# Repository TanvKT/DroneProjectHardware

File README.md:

# DroneProjectHardware
PCB schematic and design for Drone Project

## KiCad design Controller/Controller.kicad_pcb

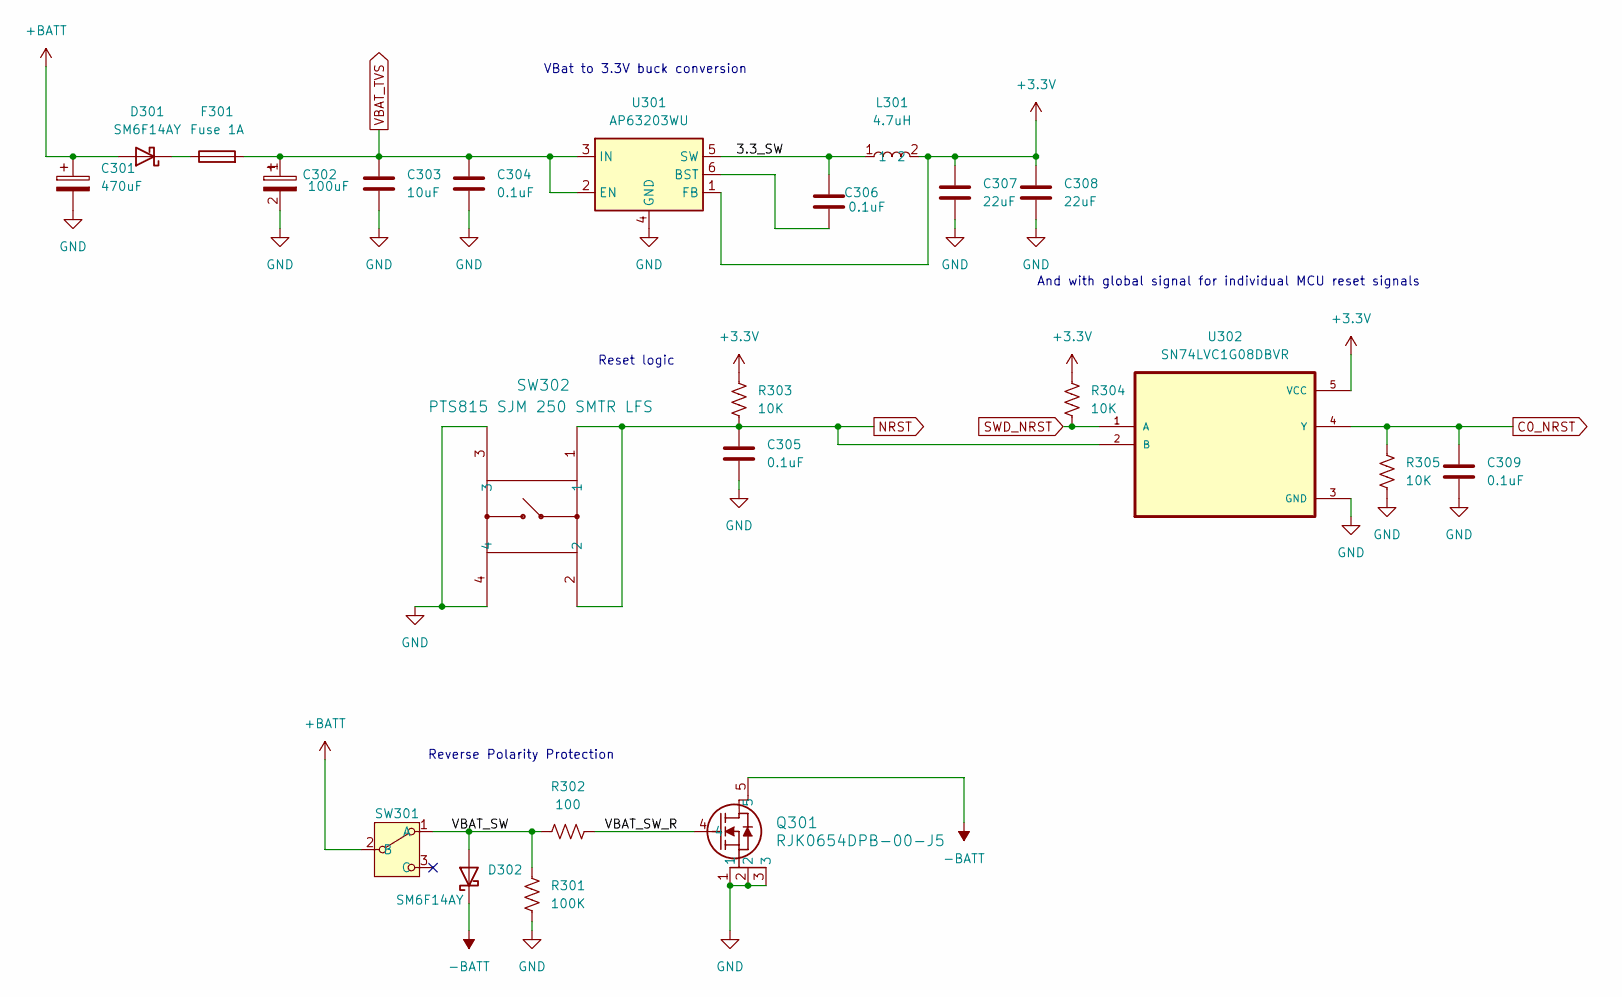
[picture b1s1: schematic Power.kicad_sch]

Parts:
C301: 470uF; CP_Elec_10x10.5
C302: 100uF; CAP_A768EB_6.8x6.8_KEM
C303: 10uF; C_1206_3216Metric
C304, C305, C306, C309: 0.1uF; C_0402_1005Metric
C307, C308: 22uF; C_0603_1608Metric
D301, D302: SM6F14AY; D_SOD-128
F301: Fuse 1A; Fuse_1812_4532Metric
L301: 4.7uH; IND_VLS6045EX-4R7M_TDK
Q301: RJK0654DPB-00-J5; LFPAK_REN
R301: 100K; R_0402_1005Metric
R302: 100; R_0201_0603Metric
R303, R304, R305: 10K; R_0402_1005Metric
SW301: SW_EG1218
SW302: PTS815 SJM 250 SMTR LFS; SW4_PTS815 SJM 250 SMTR LFS_CNK
U301: AP63203WU; TSOT-23-6
U302: SN74LVC1G08DBVR; SOT95P280X145-5N

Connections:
+3.3V: C307.1, C308.1, L301.2, R303.2, R304.2, U301.1 (FB), U302.5 (VCC); also elsewhere on the board
+BATT: C301.1, D301.2 (A), SW301.2 (B); also elsewhere on the board
-BATT: D302.1 (K), Q301.5; also elsewhere on the board
/Power/3.3_SW: C306.2, L301.1, U301.5 (SW)
/Power/VBAT_SW: D302.2 (A), R301.1, R302.1, SW301.1 (A)
/Power/VBAT_SW_R: Q301.4, R302.2
C0_NRST: C309.1, R305.2, U302.4 (Y); also elsewhere on the board
GND: C301.2, C302.2, C303.2, C304.2, C305.2, C307.2, C308.2, C309.2, Q301.1, Q301.2, Q301.3, R301.2, R305.1, SW302.3, SW302.4, U301.4 (GND), U302.3 (GND); also elsewhere on the board
NRST: C305.1, R303.1, SW302.1, SW302.2, U302.2 (B)
unnamed: D301.1 (K), F301.1
unnamed: C306.1, U301.6 (BST)
SWD_NRST: R304.1, U302.1 (A); also elsewhere on the board
VBAT_TVS: C302.1, C303.1, C304.1, F301.2, U301.2 (EN), U301.3 (IN); also elsewhere on the board

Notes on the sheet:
Reverse Polarity Protection
VBat to 3.3V buck conversion
And with global signal for individual MCU reset signals
Reset logic

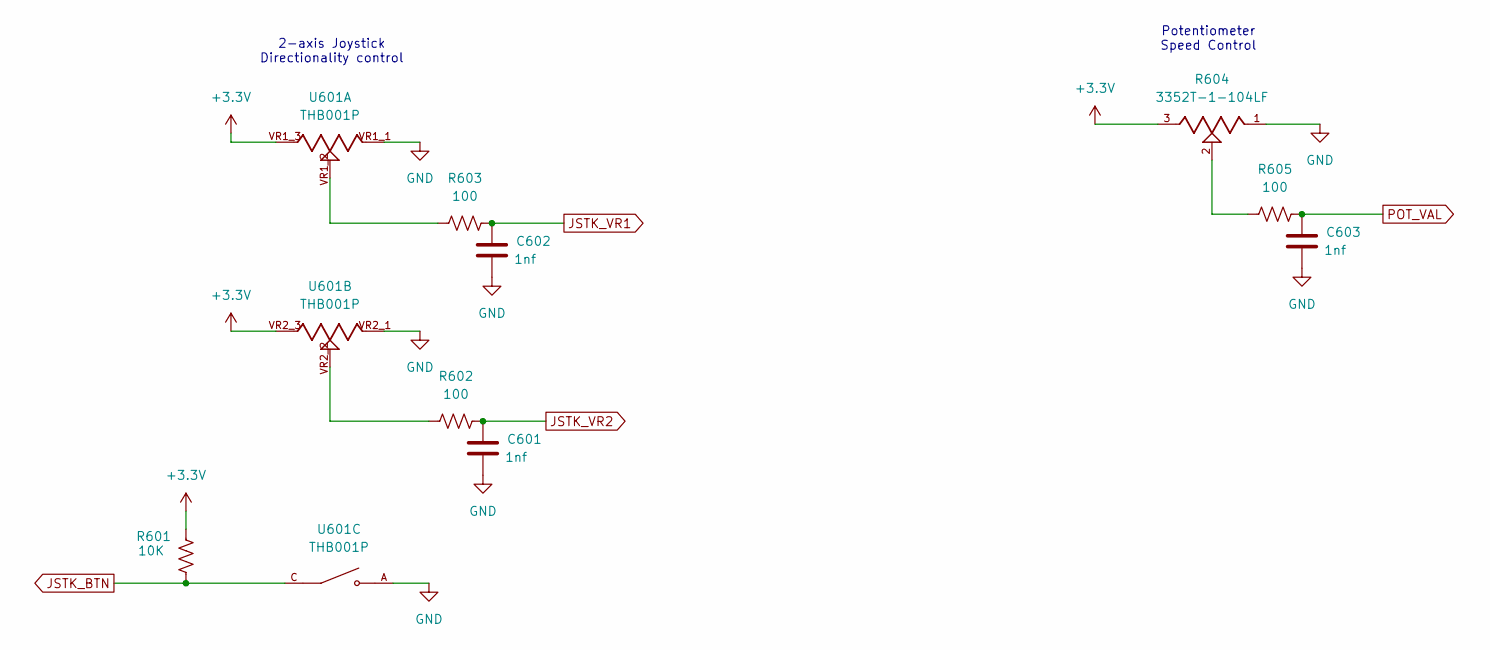
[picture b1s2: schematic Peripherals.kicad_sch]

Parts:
C601, C602, C603: 1nf; C_0402_1005Metric
R601: 10K; R_0402_1005Metric
R602, R603, R605: 100; R_0402_1005Metric
R604: 3352T-1-104LF; TRIM_3352T-1-104LF; PARTREV 08/19
U601: THB001P; CNK_THB001P; PARTREV 27 Jan 22

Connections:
+3.3V: R601.2, R604.3, U601.VR1_3, U601.VR2_3; also elsewhere on the board
GND: C601.2, C602.2, C603.2, R604.1, U601.A, U601.VR1_1, U601.VR2_1; also elsewhere on the board
JSTK_BTN: R601.1, U601.C; also elsewhere on the board
JSTK_VR1: C602.1, R603.2; also elsewhere on the board
JSTK_VR2: C601.1, R602.2; also elsewhere on the board
unnamed: R602.1, U601.VR2_2
unnamed: R603.1, U601.VR1_2
unnamed: R604.2, R605.1
POT_VAL: C603.1, R605.2; also elsewhere on the board

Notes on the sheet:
2-axis Joystick Directionality control
Potentiometer Speed Control

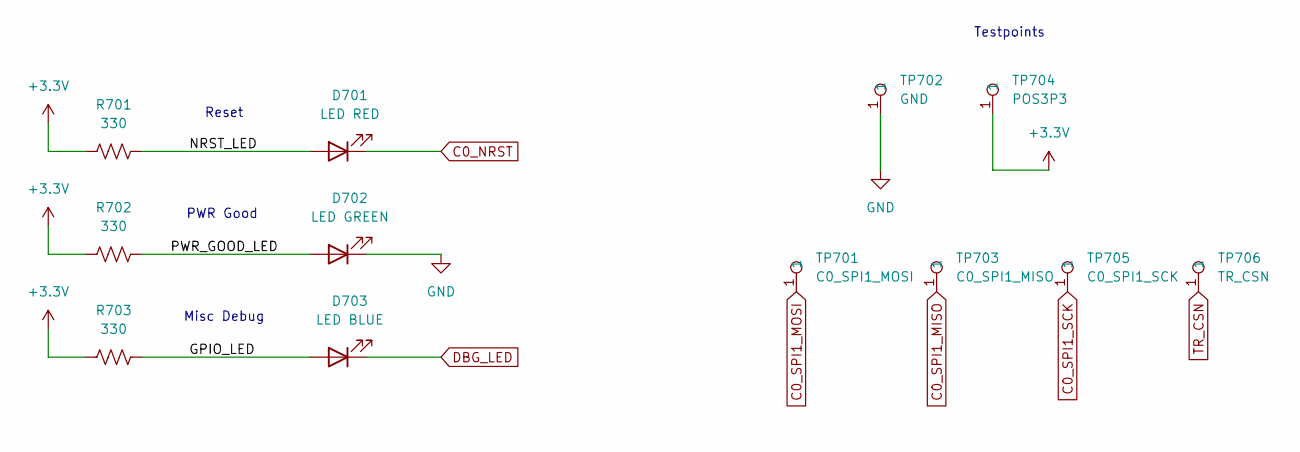
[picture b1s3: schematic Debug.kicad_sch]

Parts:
D701: LED RED; LED_0603_1608Metric
D702: LED GREEN; LED_0603_1608Metric
D703: LED BLUE; LED_0603_1608Metric
R701, R702, R703: 330; R_0402_1005Metric
TP701: C0_SPI1_MOSI; Testpoint 1.6mm x 0.8mm
TP702: GND; Testpoint 1.6mm x 0.8mm
TP703: C0_SPI1_MISO; Testpoint 1.6mm x 0.8mm
TP704: POS3P3; Testpoint 1.6mm x 0.8mm
TP705: C0_SPI1_SCK; Testpoint 1.6mm x 0.8mm
TP706: TR_CSN; Testpoint 1.6mm x 0.8mm

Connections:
+3.3V: R701.1, R702.1, R703.1, TP704.1; also elsewhere on the board
/Debug/GPIO_LED: D703.2 (A), R703.2
/Debug/NRST_LED: D701.2 (A), R701.2
/Debug/PWR_GOOD_LED: D702.2 (A), R702.2
C0_NRST: D701.1 (K); also elsewhere on the board
C0_SPI1_MISO: TP703.1; also elsewhere on the board
C0_SPI1_MOSI: TP701.1; also elsewhere on the board
C0_SPI1_SCK: TP705.1; also elsewhere on the board
DBG_LED: D703.1 (K); also elsewhere on the board
GND: D702.1 (K), TP702.1; also elsewhere on the board
TR_CSN: TP706.1; also elsewhere on the board

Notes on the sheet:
Misc Debug
Testpoints
PWR Good
Reset

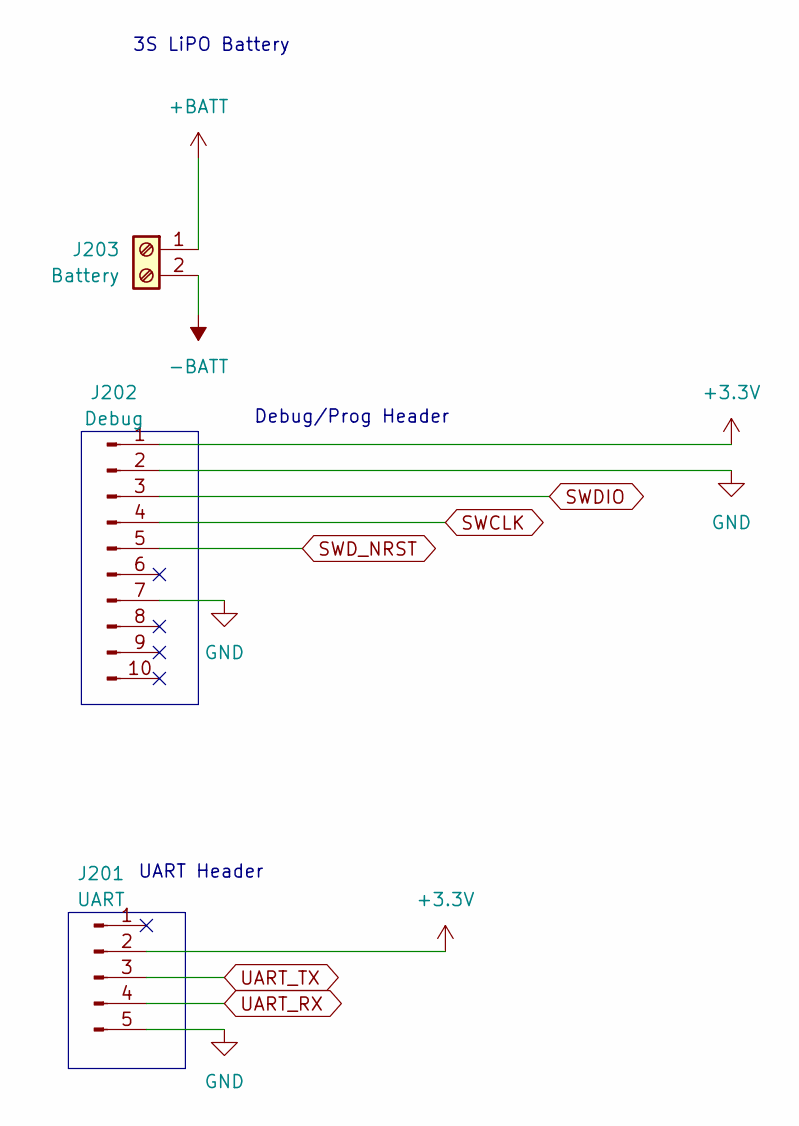
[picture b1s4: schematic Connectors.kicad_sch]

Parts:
J201: UART; PinHeader_1x05_P2.54mm_Vertical
J202: Debug; PinHeader_2x05_P2.54mm_Vertical
J203: Battery; CUI_TB002-500-02BE

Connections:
+3.3V: J201.2, J202.1; also elsewhere on the board
+BATT: J203.1; also elsewhere on the board
-BATT: J203.2; also elsewhere on the board
GND: J201.5, J202.2, J202.7; also elsewhere on the board
SWCLK: J202.4; also elsewhere on the board
SWDIO: J202.3; also elsewhere on the board
SWD_NRST: J202.5; also elsewhere on the board
UART_RX: J201.4; also elsewhere on the board
UART_TX: J201.3; also elsewhere on the board

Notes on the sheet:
UART Header
3S LiPO Battery
Debug/Prog Header

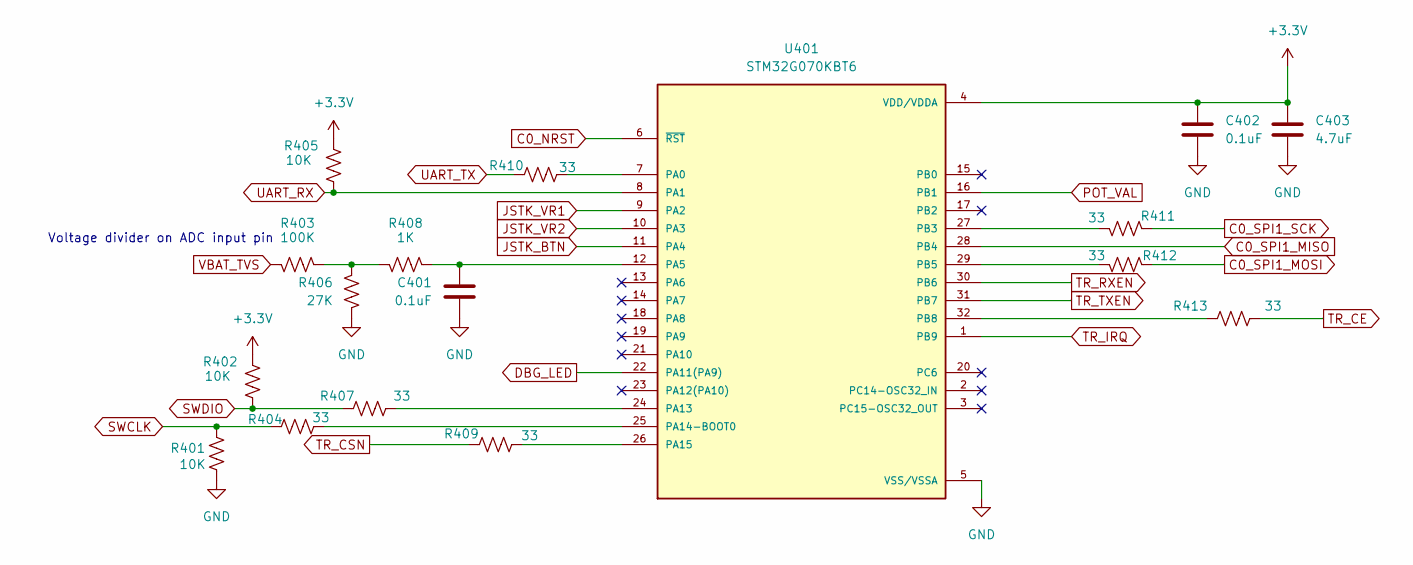
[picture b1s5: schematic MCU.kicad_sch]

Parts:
C401, C402: 0.1uF; C_0402_1005Metric
C403: 4.7uF; C_0805_2012Metric
R401, R402, R405: 10K; R_0402_1005Metric
R403: 100K; R_0402_1005Metric
R404, R407, R409, R410, R411, R412, R413: 33; R_0402_1005Metric
R406: 27K; R_0402_1005Metric
R408: 1K; R_0402_1005Metric
U401: STM32G070KBT6; QFP80P900X900X160-32N; PARTREV 2

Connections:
+3.3V: C402.1, C403.1, R402.2, R405.2, U401.4 (VDD/VDDA); also elsewhere on the board
C0_NRST: U401.6 (~RST); also elsewhere on the board
C0_SPI1_MISO: U401.28 (PB4); also elsewhere on the board
C0_SPI1_MOSI: R412.1; also elsewhere on the board
C0_SPI1_SCK: R411.1; also elsewhere on the board
DBG_LED: U401.22 (PA11(PA9)); also elsewhere on the board
GND: C401.2, C402.2, C403.2, R401.1, R406.1, U401.5 (VSS/VSSA); also elsewhere on the board
JSTK_BTN: U401.11 (PA4); also elsewhere on the board
JSTK_VR1: U401.9 (PA2); also elsewhere on the board
JSTK_VR2: U401.10 (PA3); also elsewhere on the board
unnamed: R403.1, R406.2, R408.2
unnamed: R410.2, U401.7 (PA0)
unnamed: C401.1, R408.1, U401.12 (PA5)
unnamed: R407.2, U401.24 (PA13)
unnamed: R404.2, U401.25 (PA14-BOOT0)
unnamed: R409.2, U401.26 (PA15)
unnamed: R411.2, U401.27 (PB3)
unnamed: R412.2, U401.29 (PB5)
unnamed: R413.1, U401.32 (PB8)
POT_VAL: U401.16 (PB1); also elsewhere on the board
SWCLK: R401.2, R404.1; also elsewhere on the board
SWDIO: R402.1, R407.1; also elsewhere on the board
TR_CE: R413.2; also elsewhere on the board
TR_CSN: R409.1; also elsewhere on the board
TR_IRQ: U401.1 (PB9); also elsewhere on the board
TR_RXEN: U401.30 (PB6); also elsewhere on the board
TR_TXEN: U401.31 (PB7); also elsewhere on the board
UART_RX: R405.1, U401.8 (PA1); also elsewhere on the board
UART_TX: R410.1; also elsewhere on the board
VBAT_TVS: R403.2; also elsewhere on the board

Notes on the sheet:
Voltage divider on ADC input pin

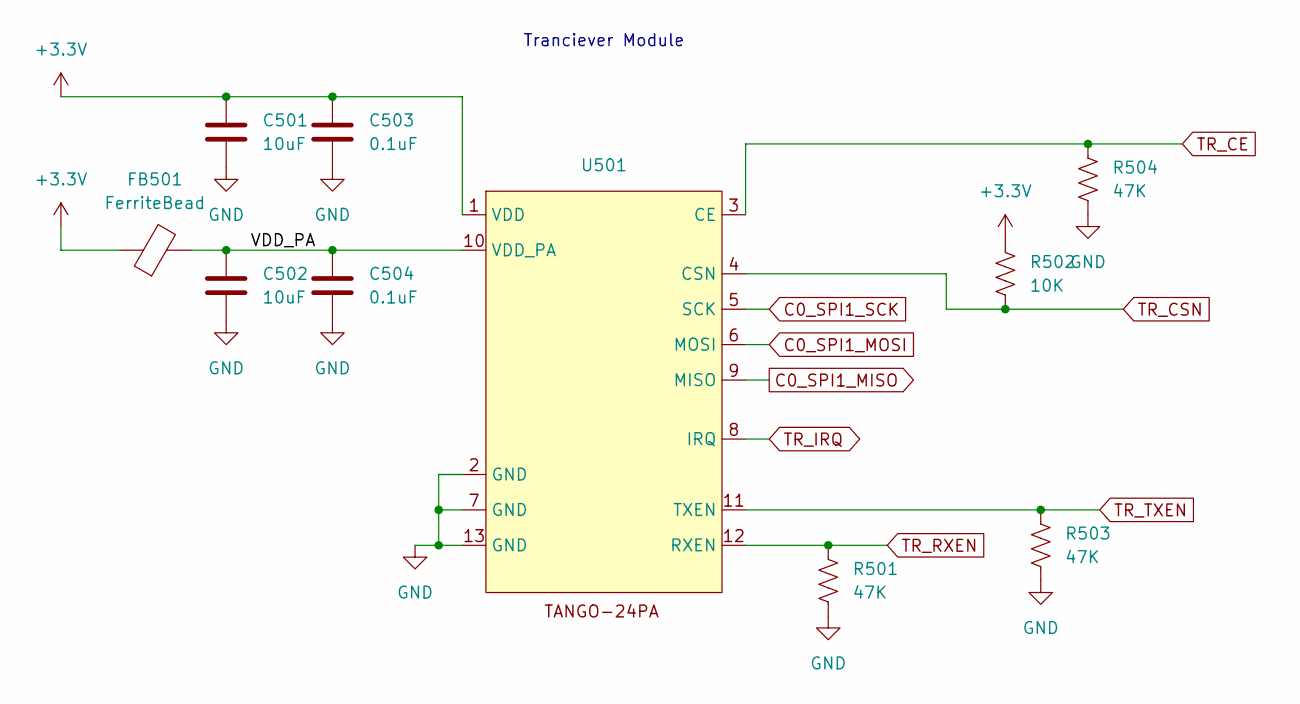
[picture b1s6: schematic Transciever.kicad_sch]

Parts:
C501, C502: 10uF; C_1206_3216Metric
C503, C504: 0.1uF; C_0402_1005Metric
FB501: FerriteBead; L_0805_2012Metric
R501, R503, R504: 47K; R_0402_1005Metric
R502: 10K; R_0402_1005Metric
U501: TANGO-24PA

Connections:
+3.3V: C501.1, C503.1, FB501.1, R502.2, U501.1 (VDD); also elsewhere on the board
/Transciever/VDD_PA: C502.1, C504.1, FB501.2, U501.10 (VDD_PA)
C0_SPI1_MISO: U501.9 (MISO); also elsewhere on the board
C0_SPI1_MOSI: U501.6 (MOSI); also elsewhere on the board
C0_SPI1_SCK: U501.5 (SCK); also elsewhere on the board
GND: C501.2, C502.2, C503.2, C504.2, R501.2, R503.2, R504.2, U501.2 (GND), U501.7 (GND), U501.13 (GND); also elsewhere on the board
TR_CE: R504.1, U501.3 (CE); also elsewhere on the board
TR_CSN: R502.1, U501.4 (CSN); also elsewhere on the board
TR_IRQ: U501.8 (IRQ); also elsewhere on the board
TR_RXEN: R501.1, U501.12 (RXEN); also elsewhere on the board
TR_TXEN: R503.1, U501.11 (TXEN); also elsewhere on the board

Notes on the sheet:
Tranciever Module

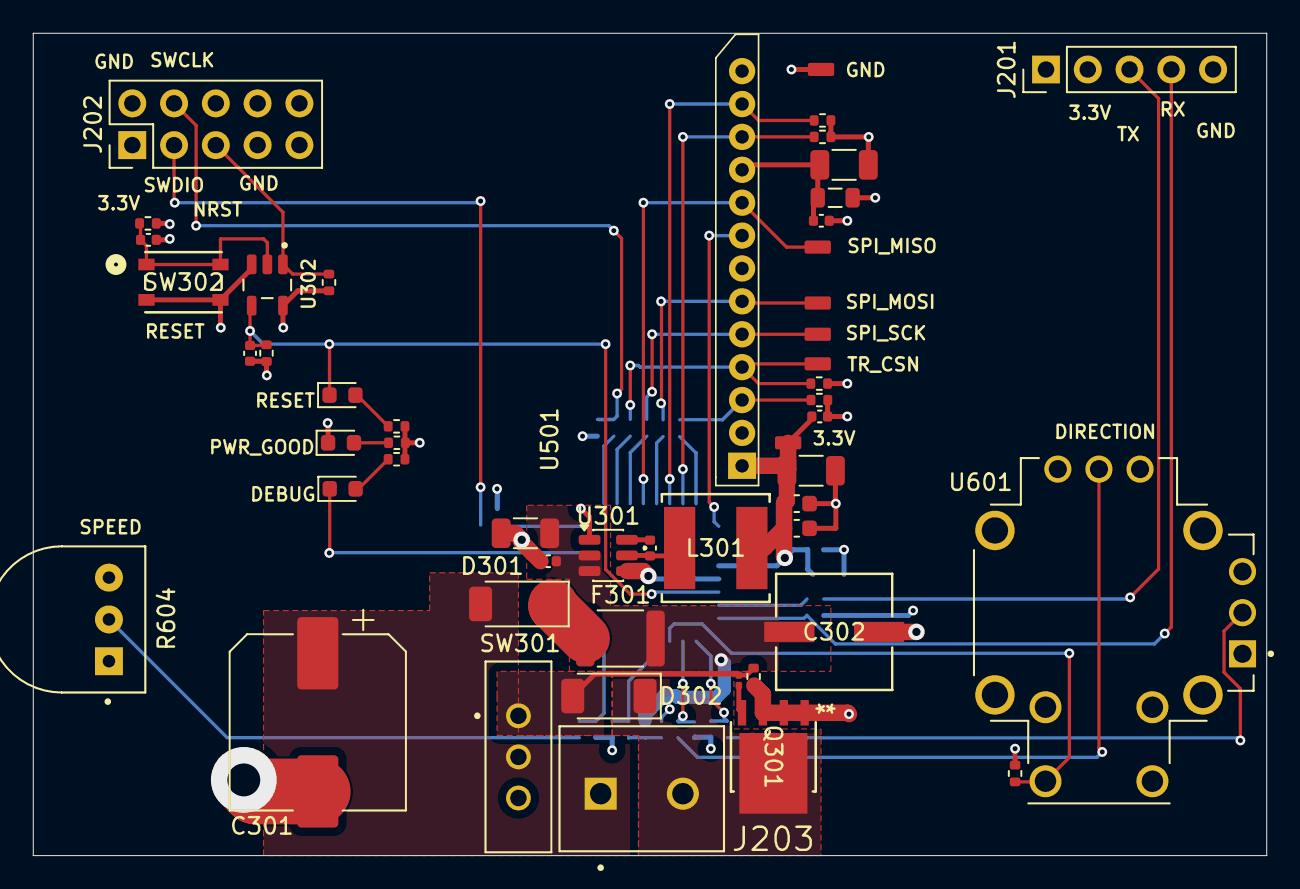
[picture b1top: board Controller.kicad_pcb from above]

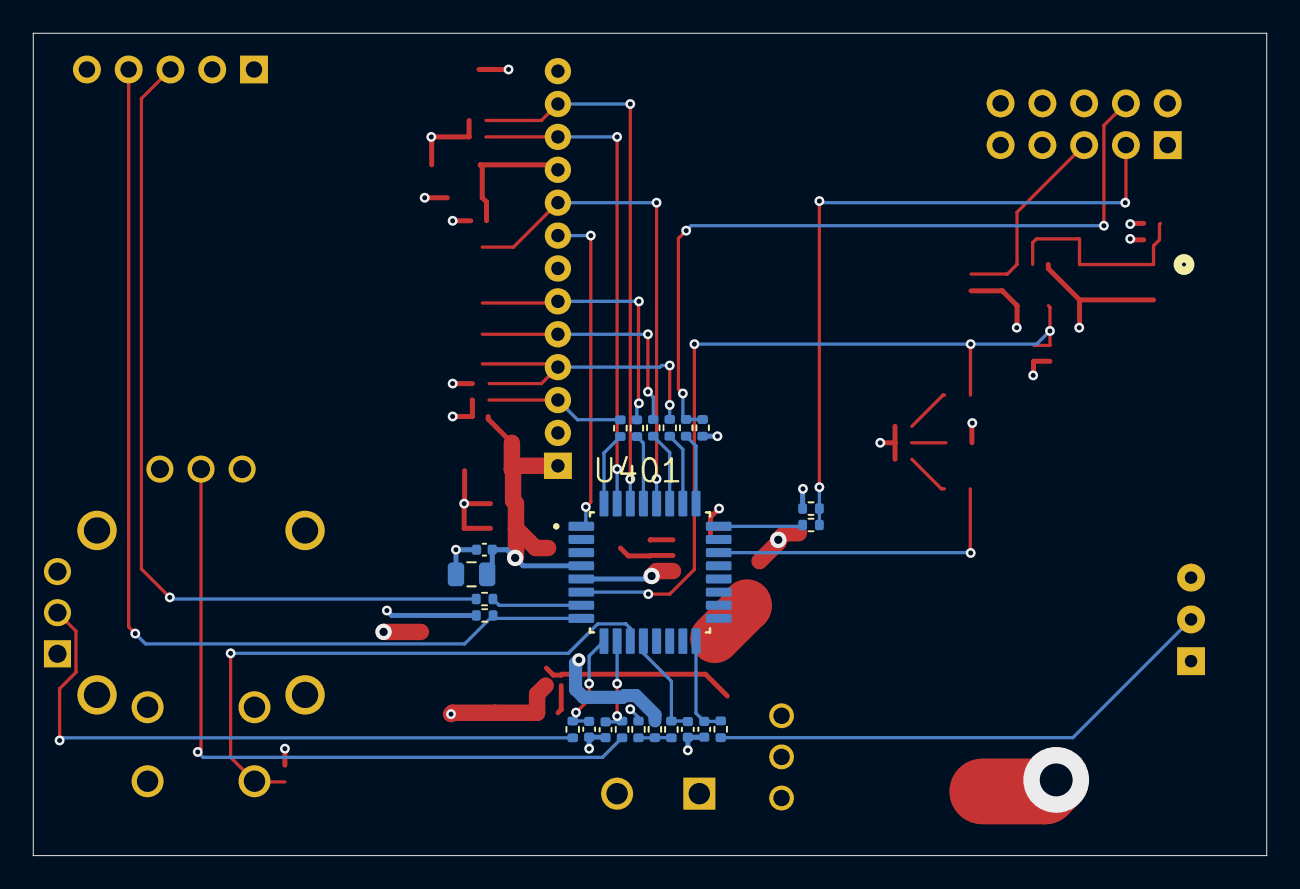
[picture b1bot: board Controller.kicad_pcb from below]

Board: 4 copper layers, 75.0 x 50.0 mm, 74 parts (23 on the bottom side), 46 nets.

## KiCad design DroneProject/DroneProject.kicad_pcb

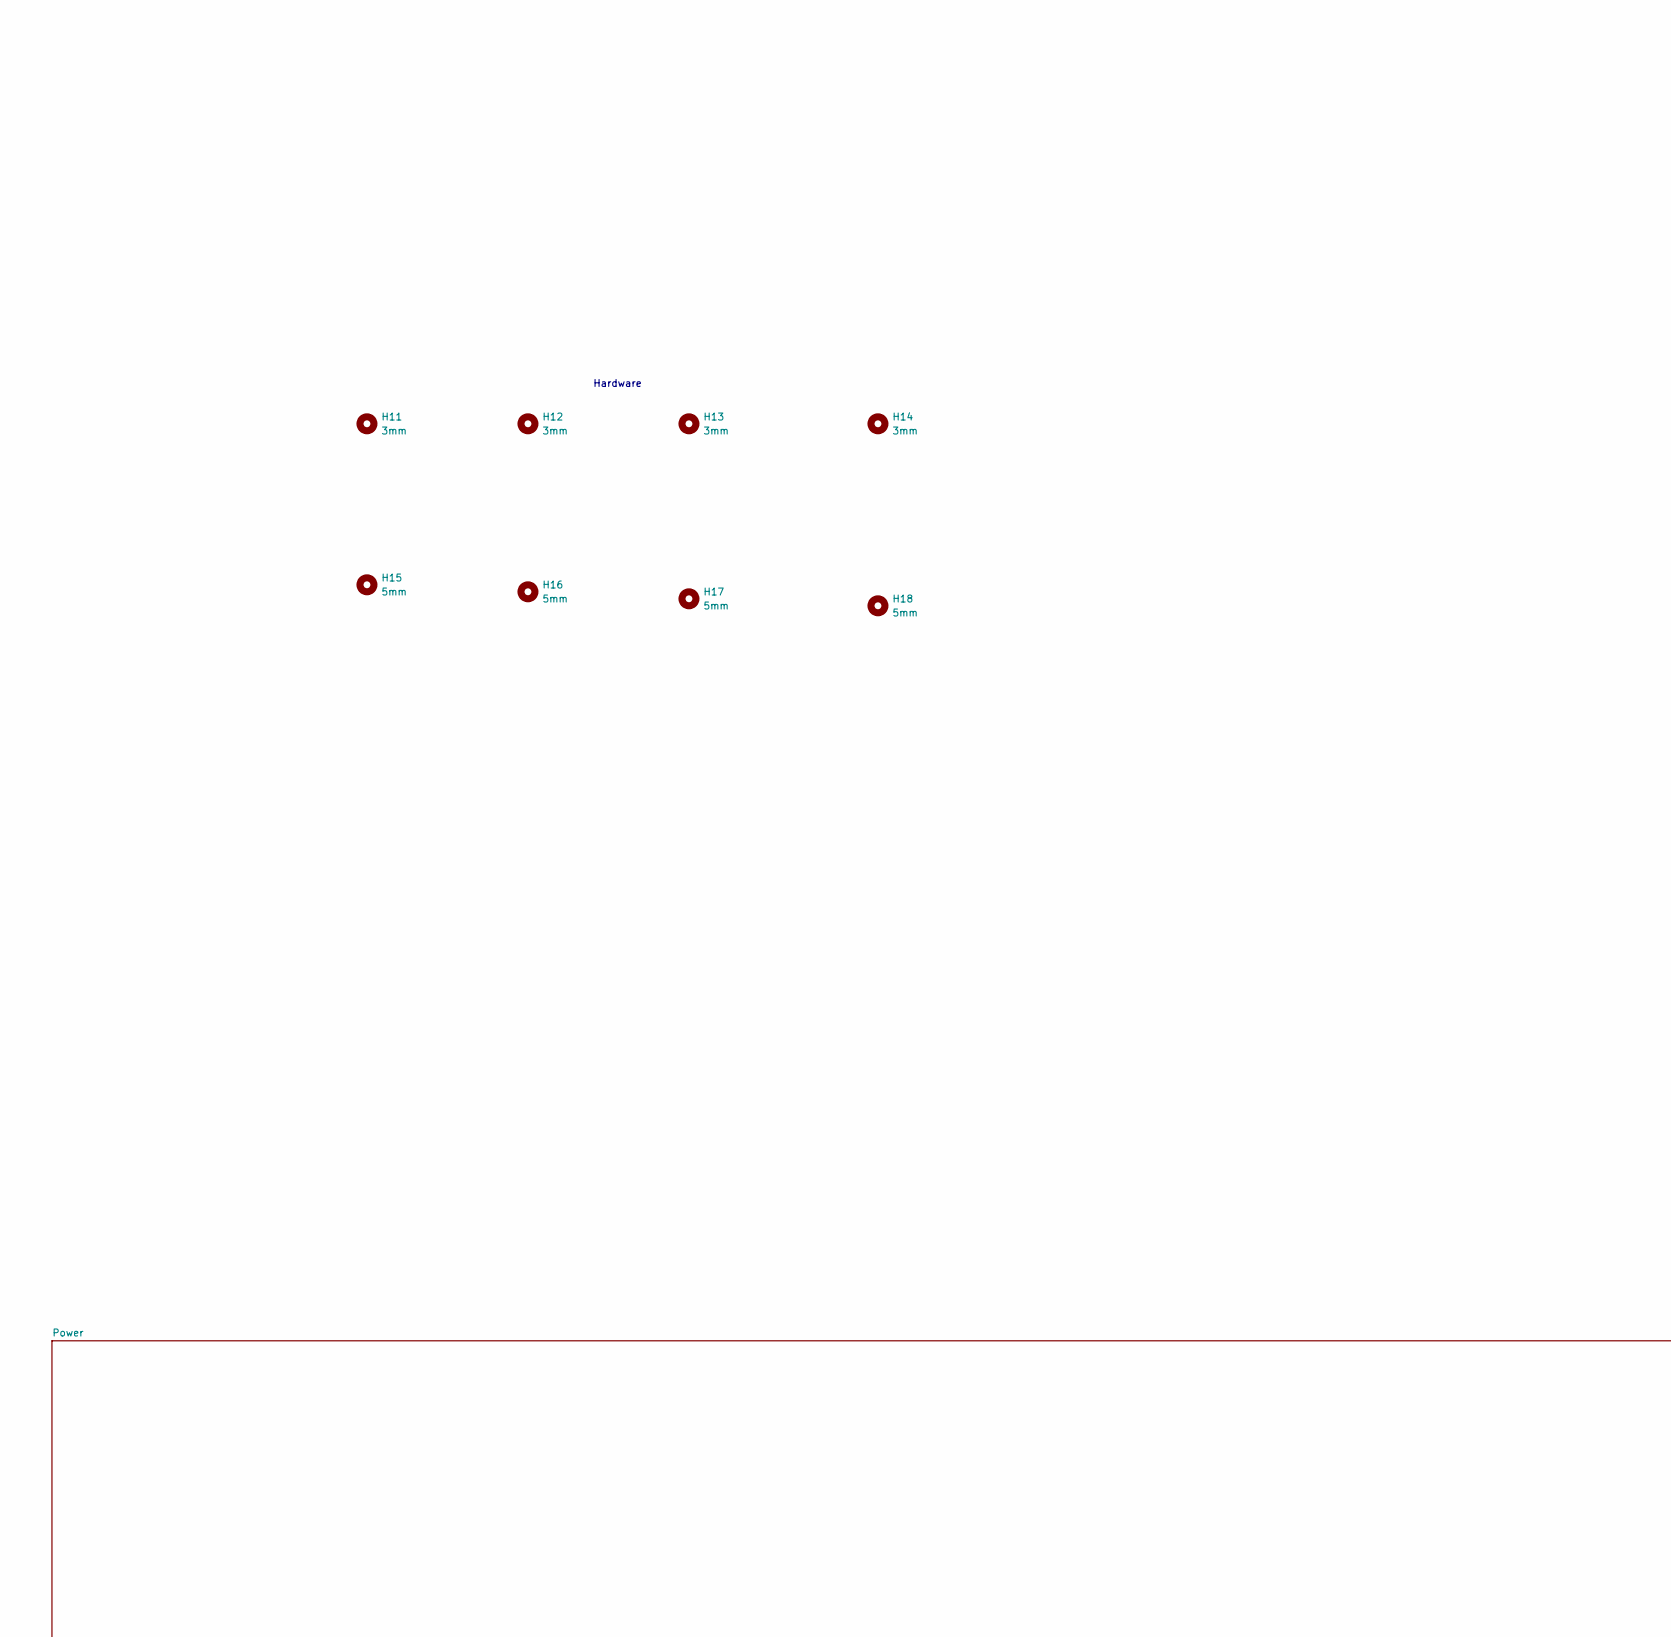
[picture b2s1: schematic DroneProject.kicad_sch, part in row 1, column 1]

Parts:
H11, H12, H13, H14: 3mm; MountingHole_3mm
H15, H16, H17, H18: 5mm; MountingHole_5mm

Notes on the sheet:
Hardware

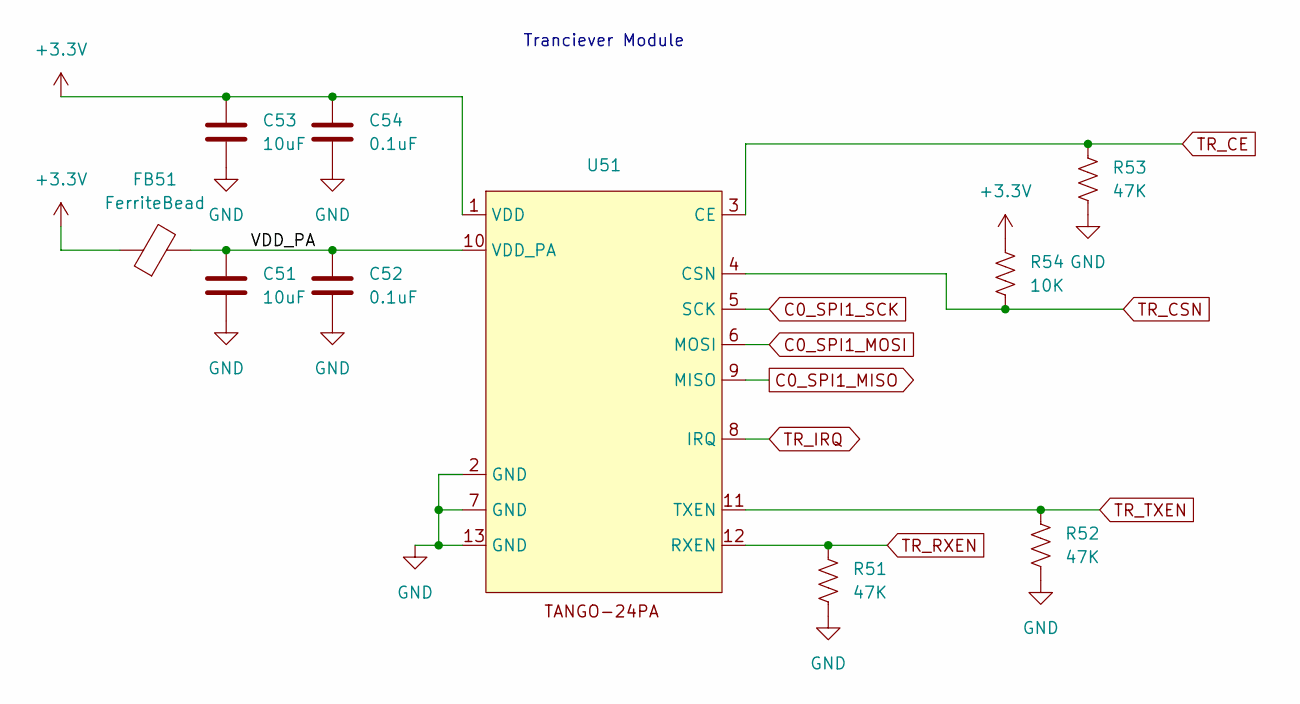
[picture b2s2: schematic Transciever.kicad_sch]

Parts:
C51, C53: 10uF; C_1206_3216Metric
C52, C54: 0.1uF; C_0402_1005Metric
FB51: FerriteBead; L_0805_2012Metric
R51, R52, R53: 47K; R_0402_1005Metric
R54: 10K; R_0402_1005Metric
U51: TANGO-24PA

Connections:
+3.3V: C53.1, C54.1, FB51.1, R54.2, U51.1 (VDD); also elsewhere on the board
/Transciever/VDD_PA: C51.1, C52.1, FB51.2, U51.10 (VDD_PA)
C0_SPI1_MISO: U51.9 (MISO); also elsewhere on the board
C0_SPI1_MOSI: U51.6 (MOSI); also elsewhere on the board
C0_SPI1_SCK: U51.5 (SCK); also elsewhere on the board
GND: C51.2, C52.2, C53.2, C54.2, R51.2, R52.2, R53.2, U51.2 (GND), U51.7 (GND), U51.13 (GND); also elsewhere on the board
TR_CE: R53.1, U51.3 (CE); also elsewhere on the board
TR_CSN: R54.1, U51.4 (CSN); also elsewhere on the board
TR_IRQ: U51.8 (IRQ); also elsewhere on the board
TR_RXEN: R51.1, U51.12 (RXEN); also elsewhere on the board
TR_TXEN: R52.1, U51.11 (TXEN); also elsewhere on the board

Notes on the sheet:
Tranciever Module

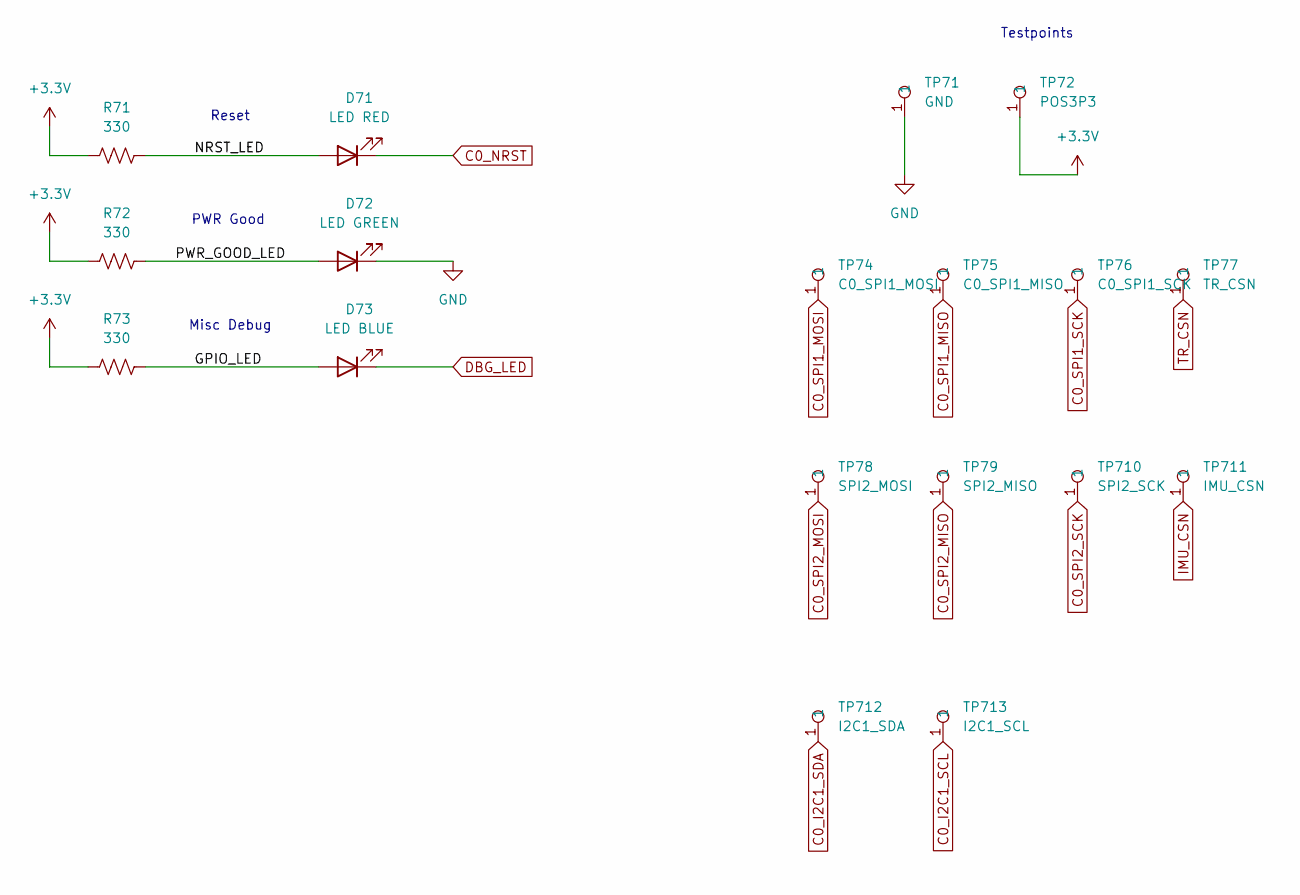
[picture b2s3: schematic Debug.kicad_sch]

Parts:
D71: LED RED; LED_0603_1608Metric
D72: LED GREEN; LED_0603_1608Metric
D73: LED BLUE; LED_0603_1608Metric
R71, R72, R73: 330; R_0402_1005Metric
TP71: GND; Testpoint 1.6mm x 0.8mm
TP72: POS3P3; Testpoint 1.6mm x 0.8mm
TP74: C0_SPI1_MOSI; Testpoint 1.6mm x 0.8mm
TP75: C0_SPI1_MISO; Testpoint 1.6mm x 0.8mm
TP76: C0_SPI1_SCK; Testpoint 1.6mm x 0.8mm
TP77: TR_CSN; Testpoint 1.6mm x 0.8mm
TP78: SPI2_MOSI; Testpoint 1.6mm x 0.8mm
TP79: SPI2_MISO; Testpoint 1.6mm x 0.8mm
TP710: SPI2_SCK; Testpoint 1.6mm x 0.8mm
TP711: IMU_CSN; Testpoint 1.6mm x 0.8mm
TP712: I2C1_SDA; Testpoint 1.6mm x 0.8mm
TP713: I2C1_SCL; Testpoint 1.6mm x 0.8mm

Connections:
+3.3V: R71.1, R72.1, R73.1, TP72.1; also elsewhere on the board
/Debug/GPIO_LED: D73.2 (A), R73.2
/Debug/NRST_LED: D71.2 (A), R71.2
/Debug/PWR_GOOD_LED: D72.2 (A), R72.2
C0_I2C1_SCL: TP713.1; also elsewhere on the board
C0_I2C1_SDA: TP712.1; also elsewhere on the board
C0_NRST: D71.1 (K); also elsewhere on the board
C0_SPI1_MISO: TP75.1; also elsewhere on the board
C0_SPI1_MOSI: TP74.1; also elsewhere on the board
C0_SPI1_SCK: TP76.1; also elsewhere on the board
C0_SPI2_MISO: TP79.1; also elsewhere on the board
C0_SPI2_MOSI: TP78.1; also elsewhere on the board
C0_SPI2_SCK: TP710.1; also elsewhere on the board
DBG_LED: D73.1 (K); also elsewhere on the board
GND: D72.1 (K), TP71.1; also elsewhere on the board
IMU_CSN: TP711.1; also elsewhere on the board
TR_CSN: TP77.1; also elsewhere on the board

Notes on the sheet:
Misc Debug
Reset
Testpoints
PWR Good

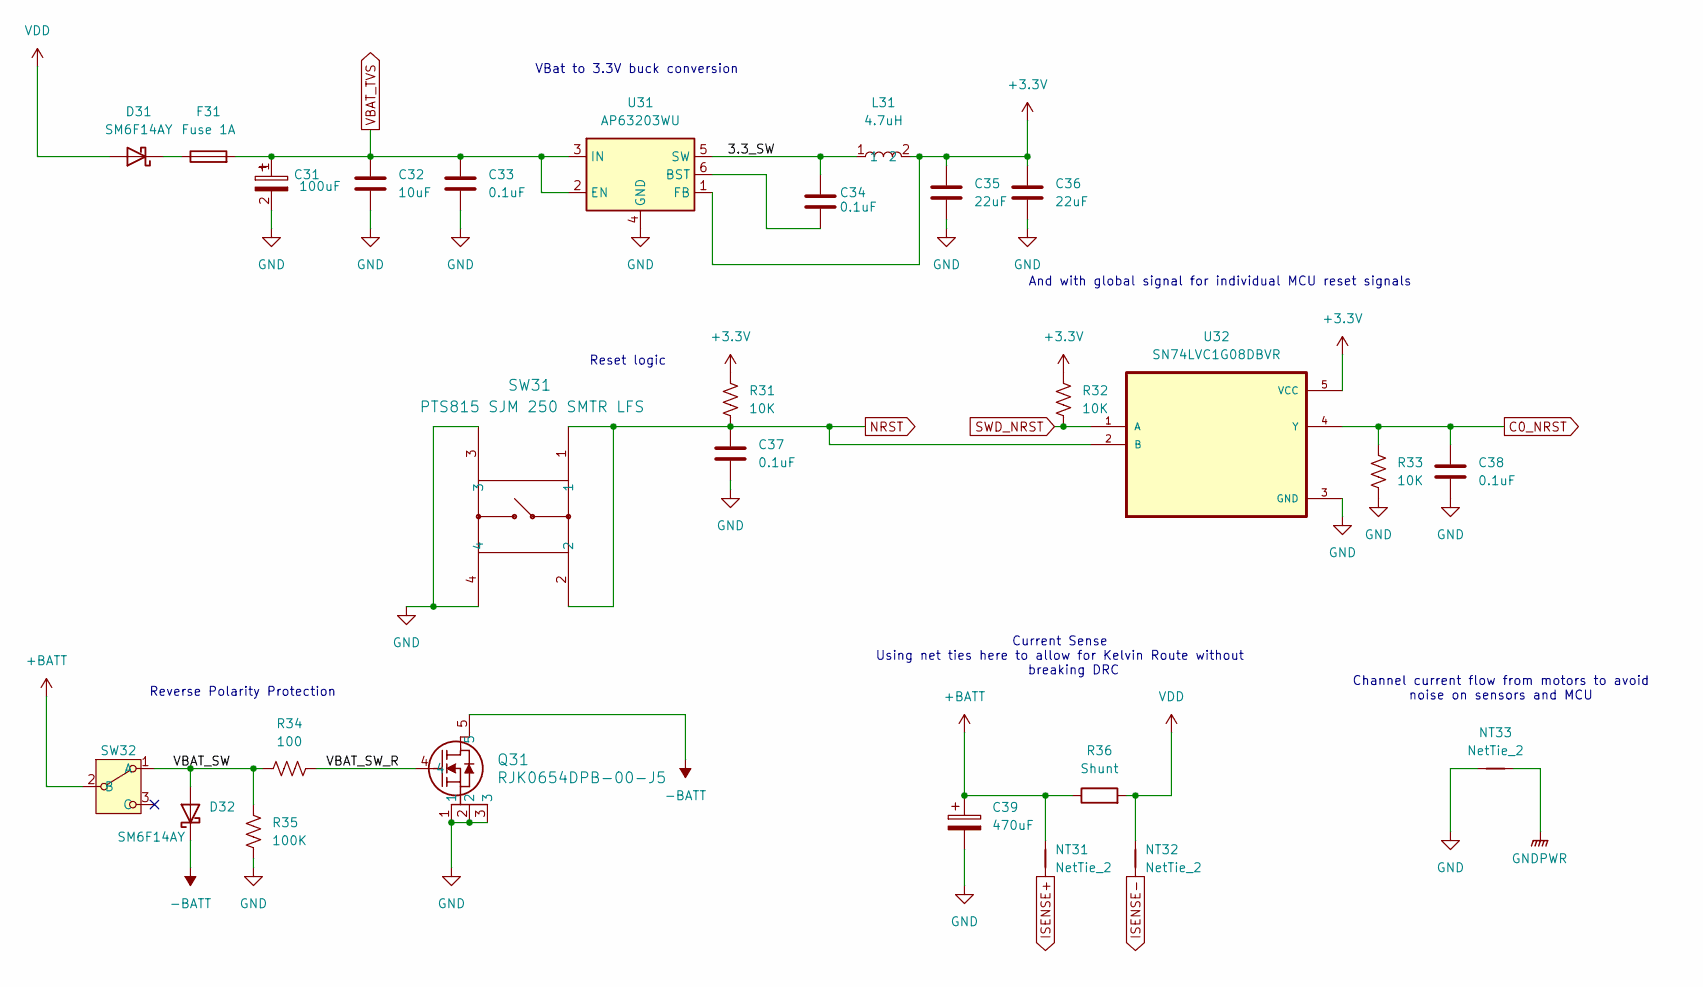
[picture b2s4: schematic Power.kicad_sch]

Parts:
C31: 100uF; CAP_A768EB_6.8x6.8_KEM
C32: 10uF; C_1206_3216Metric
C33, C34, C37, C38: 0.1uF; C_0402_1005Metric
C35, C36: 22uF; C_0603_1608Metric
C39: 470uF; CP_Elec_10x10.5
D31, D32: SM6F14AY; D_SOD-128
F31: Fuse 1A; Fuse_1812_4532Metric
L31: 4.7uH; IND_VLS6045EX-4R7M_TDK
NT31, NT32: NetTie_2; NetTie-2_SMD_Pad0.5mm
NT33: NetTie_2; NetTie-2_SMD_Pad2.0mm
Q31: RJK0654DPB-00-J5; LFPAK_REN
R31, R32, R33: 10K; R_0402_1005Metric
R34: 100; R_0201_0603Metric
R35: 100K; R_0402_1005Metric
R36: Shunt; R_2010_5025Metric
SW31: PTS815 SJM 250 SMTR LFS; SW4_PTS815 SJM 250 SMTR LFS_CNK
SW32: SW_EG1218
U31: AP63203WU; TSOT-23-6
U32: SN74LVC1G08DBVR; SOT95P280X145-5N

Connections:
+3.3V: C35.1, C36.1, L31.2, R31.2, R32.2, U31.1 (FB), U32.5 (VCC); also elsewhere on the board
+BATT: C39.1, NT31.2, R36.1, SW32.2 (B); also elsewhere on the board
-BATT: D32.1 (K), Q31.5; also elsewhere on the board
/Power/3.3_SW: C34.2, L31.1, U31.5 (SW)
/Power/VBAT_SW: D32.2 (A), R34.1, R35.1, SW32.1 (A)
/Power/VBAT_SW_R: Q31.4, R34.2
C0_NRST: C38.1, R33.2, U32.4 (Y); also elsewhere on the board
GND: C31.2, C32.2, C33.2, C35.2, C36.2, C37.2, C38.2, C39.2, NT33.2, Q31.1, Q31.2, Q31.3, R33.1, R35.2, SW31.3, SW31.4, U31.4 (GND), U32.3 (GND); also elsewhere on the board
GNDPWR: NT33.1; also elsewhere on the board
ISENSE+: NT31.1; also elsewhere on the board
ISENSE-: NT32.1; also elsewhere on the board
NRST: C37.1, R31.1, SW31.1, SW31.2, U32.2 (B)
unnamed: D31.1 (K), F31.1
unnamed: C34.1, U31.6 (BST)
SWD_NRST: R32.1, U32.1 (A); also elsewhere on the board
VBAT_TVS: C31.1, C32.1, C33.1, F31.2, U31.2 (EN), U31.3 (IN); also elsewhere on the board
VDD: D31.2 (A), NT32.2, R36.2; also elsewhere on the board

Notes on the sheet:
And with global signal for individual MCU reset signals
Reset logic
Reverse Polarity Protection
VBat to 3.3V buck conversion
Current Sense Using net ties here to allow for Kelvin Route without breaking DRC
Channel current flow from motors to avoid noise on sensors and MCU
